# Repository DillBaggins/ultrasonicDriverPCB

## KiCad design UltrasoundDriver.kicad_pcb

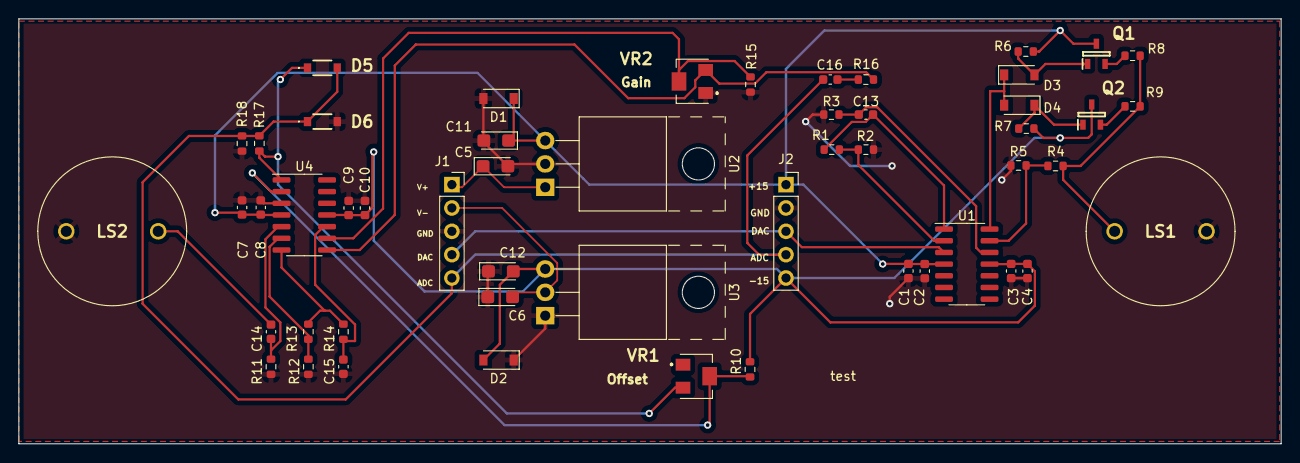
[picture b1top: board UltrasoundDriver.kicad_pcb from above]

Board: 2 copper layers, 137.3 x 46.2 mm, 52 parts (0 on the bottom side), 27 nets.

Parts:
C1, C4, C7, C10, C14, C15: 10n; C_0603_1608Metric
C2, C3, C8, C9, C13, C16: 100n; C_0603_1608Metric
C5: 0.33u; CP_EIA-3216-18_Kemet-A
C6: 2.2u; CP_EIA-3216-18_Kemet-A
C11: 0.1u; CP_EIA-3216-18_Kemet-A
C12: 1u; CP_EIA-3216-18_Kemet-A
D1, D2, D3, D4: 1N4148W; D_SOD-123
D5, D6: B5819W.SL; B5819WSL
J1, J2: Conn_01x05_Female; PinSocket_1x05_P2.54mm_Vertical
LS1, LS2: 400ST16M
Q1: SS8050-G; SOT95P240X115-3N
Q2: S8550; SOT95P240X115-3N
R1: 33k; R_0603_1608Metric
R2: 12k; R_0603_1608Metric
R3: 100k; R_0603_1608Metric
R4: 6.8k; R_0603_1608Metric
R5, R10, R16, R17, R18: 10k; R_0603_1608Metric
R6, R7, R12: 1k; R_0603_1608Metric
R8, R9, R15: 100; R_0603_1608Metric
R11: 470; R_0603_1608Metric
R13: 390k; R_0603_1608Metric
R14: 330; R_0603_1608Metric
U1, U4: MC33079; SOIC-14_3.9x8.7mm_P1.27mm
U2: L7815; TO-220-3_Horizontal_TabUp
U3: L7915; TO-220-3_Horizontal_TabUp
VR1, VR2: 3224W-1-103E; 3224W1205E

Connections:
3.3V: D5.1, R17.2, U4.1, VR1.3 (CW)
+15V: C1.1, C2.1, C7.1, C8.1, C11.1, D1.1 (K), J2.1, Q1.3, R6.1, U1.4 (V+), U2.3 (OUT), U4.4 (V+)
-15V: C3.1, C4.1, C9.1, C10.1, C12.2, D2.2 (A), J2.5, Q2.3, R7.2, R10.2, U1.11 (V-), U3.3 (VO), U4.11 (V-)
GND: C1.2, C2.2, C3.2, C4.2, C5.2, C6.1, C7.2, C8.2, C9.2, C10.2, C11.2, C12.1, C15.1, D1.2 (A), D2.1 (K), D6.2, J1.3, J2.2, LS1.2, LS2.2, R2.2, R3.1, R5.2, R11.2, R12.2, R15.2, R18.1, U2.2 (GND), U3.1 (GND), U4.3 (+), VR2.1 (CCW)
unnamed: C13.1, R3.2, U1.12 (+)
unnamed: C13.2, R1.1, U1.1
unnamed: C14.1, R11.1, U4.5 (+)
unnamed: C14.2, LS2.1
unnamed: C15.2, R14.2, U4.10 (+)
unnamed: C16.2, R16.1
unnamed: D3.1 (K), D4.2 (A), U1.14
unnamed: D3.2 (A), Q1.1, R6.2
unnamed: D4.1 (K), Q2.1, R7.1
unnamed: LS1.1, R4.1, R8.2, R9.2
unnamed: Q1.2, R8.1
unnamed: Q2.2, R9.1
unnamed: R1.2, R2.1, U1.2 (-)
unnamed: R4.2, R5.1, U1.13 (-)
unnamed: R10.1, U4.2 (-), VR1.2 (WIPER)
unnamed: R12.1, R13.1, U4.6 (-)
unnamed: R13.2, R14.1, U4.7
unnamed: R15.1, U4.9 (-), VR2.2 (WIPER)
unnamed: R16.2, U4.8, VR2.3 (CW)
powerIn+: C5.1, J1.1, U2.1 (IN)
powerIn-: C6.2, J1.2, U3.2 (VI)
sigIn: J1.4, J2.3, U1.3 (+)
sigOut: C16.1, D5.2, D6.1, J1.5, J2.4, R17.1, R18.2

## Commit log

2022-10-03 first board iteration, JLC not done yet. Lotsa DRC errors tho
2022-10-03 yeah I think this one is better, also updated resistor values after lab work
2022-10-03 need to change footprint for tantalum caps
2022-10-06 this draft has gone to justin
2022-10-06 receiver is moved to other side, I am considereding reording the op amp units to not make signal lines too long - almost certainly unnecessary since it breadboarded fine. But still
2022-10-09 updated and sent to Justin
